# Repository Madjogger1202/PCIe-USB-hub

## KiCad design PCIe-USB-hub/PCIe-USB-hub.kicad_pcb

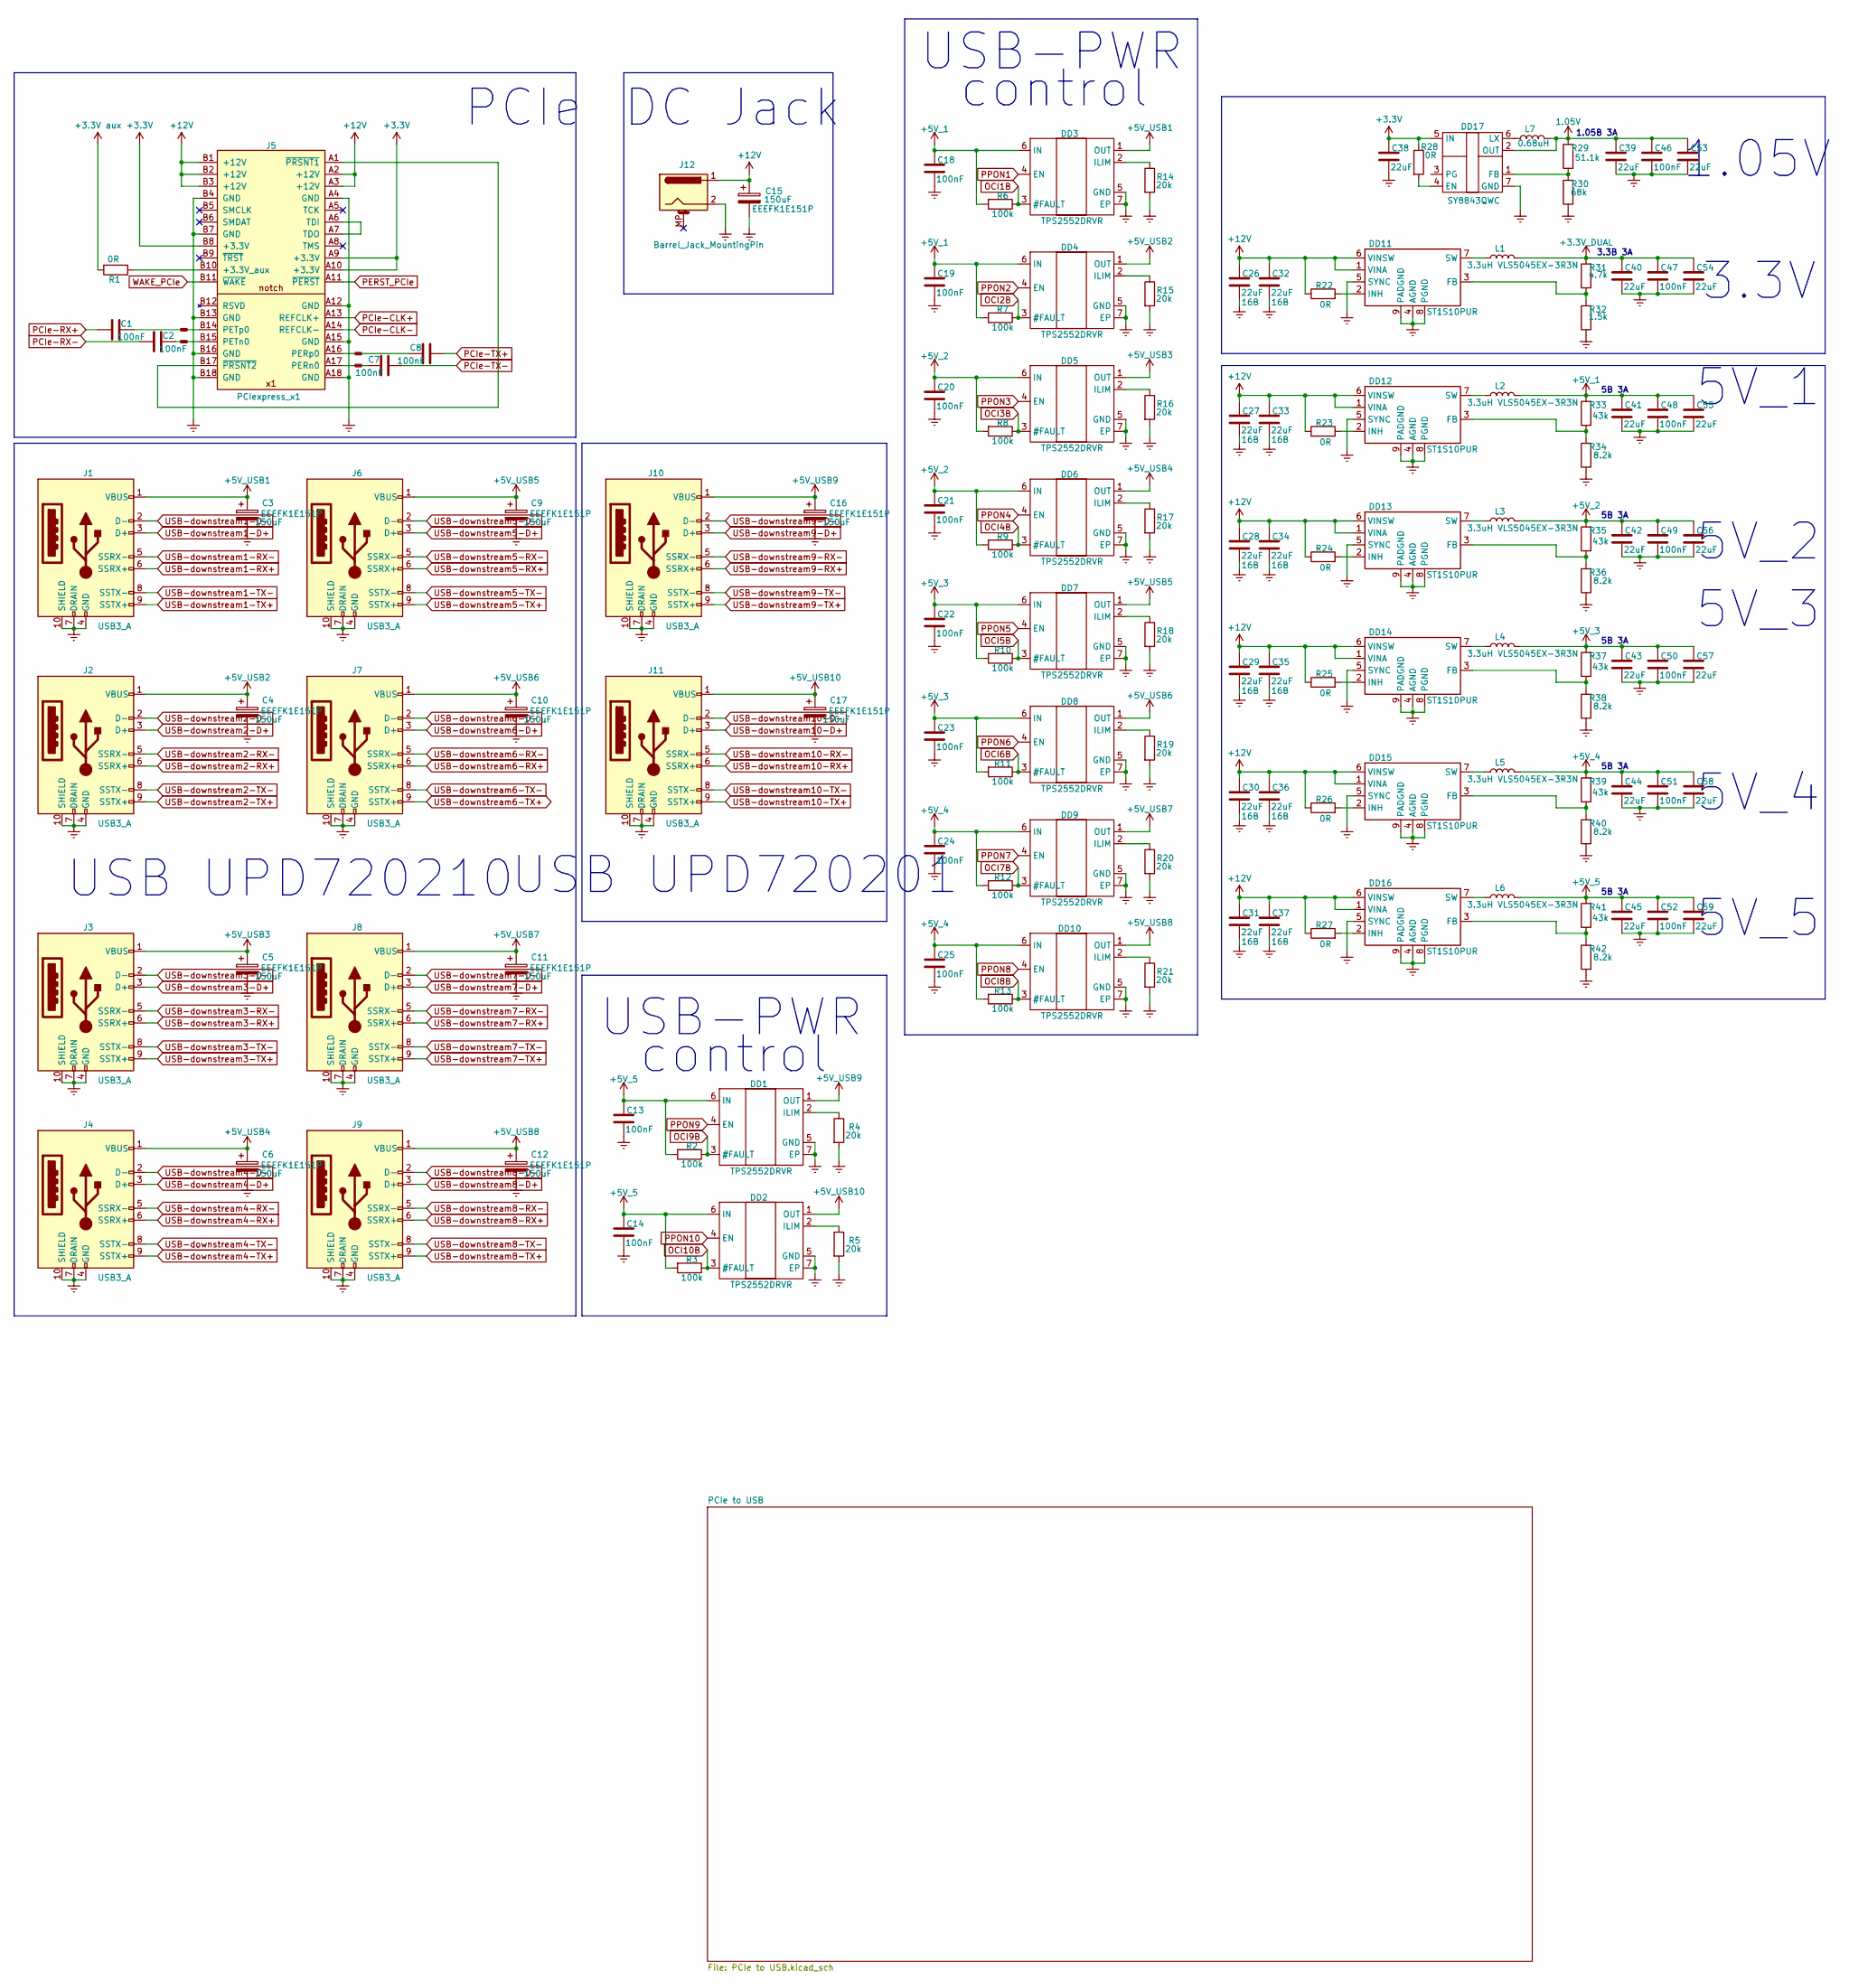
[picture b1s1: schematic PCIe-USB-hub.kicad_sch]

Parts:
C1, C2, C7, C8, C13, C14, C18, C19, C20, C21, C22, C23, C24, C25, C46, C47, C48, C49, C50, C51, C52: 100nF; C_0402_1005Metric
C3, C4, C5, C6, C9, C10, C11, C12, C15, C16, C17: EEEFK1E151P; C_Elec_8x10.2
C26, C27, C28, C29, C30, C31, C32, C33, C34, C35, C36, C37: 22uF; C_0805_2012Metric
C38, C39, C40, C41, C42, C43, C44, C45, C53, C54, C55, C56, C57, C58, C59: 22uF; C_0402_1005Metric
DD1, DD2, DD3, DD4, DD5, DD6, DD7, DD8, DD9, DD10: TPS2552DRVR; WSON-6-1EP_2x2mm_P0.65mm_EP1x1.6mm
DD11, DD12, DD13, DD14, DD15, DD16: ST1S10PUR; DFN-8-1EP_4x4mm_P0.8mm_EP2.5x3.6mm
DD17: SY8843QWC
J1, J2, J3, J4, J6, J7, J8, J9, J10, J11: USB3_A; USB3_A_Molex_48393-001
J5: PCIexpress_x1
J12: Barrel_Jack_MountingPin; BarrelJack_GCT_DCJ200-10-A_Horizontal
L1, L2, L3, L4, L5, L6: 3.3uH VLS5045EX-3R3N; COIL_5040
L7: 0.68uH; L_Cenker_CKCS4020
R1, R22, R23, R24, R25, R26, R27, R28: 0R; R_0402_1005Metric
R2, R3, R6, R7, R8, R9, R10, R11, R12, R13: 100k; R_0402_1005Metric
R4, R5, R14, R15, R16, R17, R18, R19, R20, R21: 20k; R_0402_1005Metric
R29: 51.1k; R_0402_1005Metric
R30: 68k; R_0402_1005Metric
R31: 4.7k; R_0402_1005Metric
R32: 1.5k; R_0402_1005Metric
R33, R35, R37, R39, R41: 43k; R_0402_1005Metric
R34, R36, R38, R40, R42: 8.2k; R_0402_1005Metric

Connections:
1.05V: C39.1, C46.1, C53.1, DD17.2 (OUT), L7.2, R29.2; also elsewhere on the board
+3.3V: C38.1, DD17.5 (IN), J5.A9 (+3.3V), J5.A10 (+3.3V), J5.B8 (+3.3V), R28.1
+3.3V aux: R1.2
+3.3V_DUAL: C40.1, C47.1, C54.1, L1.2, R31.2; also elsewhere on the board
+5V_1: C18.1, C19.1, C41.1, C48.1, C55.1, DD3.6 (IN), DD4.6 (IN), L2.2, R6.2, R7.2, R33.2
+5V_2: C20.1, C21.1, C42.1, C49.1, C56.1, DD5.6 (IN), DD6.6 (IN), L3.2, R8.2, R9.2, R35.2
+5V_3: C22.1, C23.1, C43.1, C50.1, C57.1, DD7.6 (IN), DD8.6 (IN), L4.2, R10.2, R11.2, R37.2
+5V_4: C24.1, C25.1, C44.1, C51.1, C58.1, DD9.6 (IN), DD10.6 (IN), L5.2, R12.2, R13.2, R39.2
+5V_5: C13.1, C14.1, C45.1, C52.1, C59.1, DD1.6 (IN), DD2.6 (IN), L6.2, R2.2, R3.2, R41.2
+5V_USB1: C3.1, DD3.1 (OUT), J1.1 (VBUS)
+5V_USB2: C4.1, DD4.1 (OUT), J2.1 (VBUS)
+5V_USB3: C5.1, DD5.1 (OUT), J3.1 (VBUS)
+5V_USB4: C6.1, DD6.1 (OUT), J4.1 (VBUS)
+5V_USB5: C9.1, DD7.1 (OUT), J6.1 (VBUS)
+5V_USB6: C10.1, DD8.1 (OUT), J7.1 (VBUS)
+5V_USB7: C11.1, DD9.1 (OUT), J8.1 (VBUS)
+5V_USB8: C12.1, DD10.1 (OUT), J9.1 (VBUS)
+5V_USB9: C16.1, DD1.1 (OUT), J10.1 (VBUS)
+5V_USB10: C17.1, DD2.1 (OUT), J11.1 (VBUS)
+12V: C15.1, C26.1, C27.1, C28.1, C29.1, C30.1, C31.1, C32.1, C33.1, C34.1, C35.1, C36.1, C37.1, DD11.1 (VINA), DD11.6 (VINSW), DD12.1 (VINA), DD12.6 (VINSW), DD13.1 (VINA), DD13.6 (VINSW), DD14.1 (VINA), DD14.6 (VINSW), DD15.1 (VINA), DD15.6 (VINSW), DD16.1 (VINA), DD16.6 (VINSW), J5.A2 (+12V), J5.A3 (+12V), J5.B1 (+12V), J5.B2 (+12V), J5.B3 (+12V), J12.1, R22.1, R23.1, R24.1, R25.1, R26.1, R27.1
Earth: C3.2, C4.2, C5.2, C6.2, C9.2, C10.2, C11.2, C12.2, C13.2, C14.2, C15.2, C16.2, C17.2, C18.2, C19.2, C20.2, C21.2, C22.2, C23.2, C24.2, C25.2, C26.2, C27.2, C28.2, C29.2, C30.2, C31.2, C32.2, C33.2, C34.2, C35.2, C36.2, C37.2, C38.2, C39.2, C40.2, C41.2, C42.2, C43.2, C44.2, C45.2, C46.2, C47.2, C48.2, C49.2, C50.2, C51.2, C52.2, C53.2, C54.2, C55.2, C56.2, C57.2, C58.2, C59.2, DD1.5 (GND), DD1.7 (EP), DD2.5 (GND), DD2.7 (EP), DD3.5 (GND), DD3.7 (EP), DD4.5 (GND), DD4.7 (EP), DD5.5 (GND), DD5.7 (EP), DD6.5 (GND), DD6.7 (EP), DD7.5 (GND), DD7.7 (EP), DD8.5 (GND), DD8.7 (EP), DD9.5 (GND), DD9.7 (EP), DD10.5 (GND), DD10.7 (EP), DD11.4 (AGND), DD11.5 (SYNC), DD11.8 (PGND), DD11.9 (PADGND), DD12.4 (AGND), DD12.5 (SYNC), DD12.8 (PGND), DD12.9 (PADGND), DD13.4 (AGND), DD13.5 (SYNC), DD13.8 (PGND), DD13.9 (PADGND), DD14.4 (AGND), DD14.5 (SYNC), DD14.8 (PGND), DD14.9 (PADGND), DD15.4 (AGND), DD15.5 (SYNC), DD15.8 (PGND), DD15.9 (PADGND), DD16.4 (AGND), DD16.5 (SYNC), DD16.8 (PGND), DD16.9 (PADGND), DD17.7 (GND), J1.4 (GND), J1.7 (DRAIN), J1.10 (SHIELD), J2.4 (GND), J2.7 (DRAIN), J2.10 (SHIELD), J3.4 (GND), J3.7 (DRAIN), J3.10 (SHIELD), J4.4 (GND), J4.7 (DRAIN), J4.10 (SHIELD), J5.A4 (GND), J5.A12 (GND), J5.A15 (GND), J5.A18 (GND), J5.B4 (GND), J5.B7 (GND), J5.B13 (GND), J5.B16 (GND), J5.B18 (GND), J6.4 (GND), J6.7 (DRAIN), J6.10 (SHIELD), J7.4 (GND), J7.7 (DRAIN), J7.10 (SHIELD), J8.4 (GND), J8.7 (DRAIN), J8.10 (SHIELD), J9.4 (GND), J9.7 (DRAIN), J9.10 (SHIELD), J10.4 (GND), J10.7 (DRAIN), J10.10 (SHIELD), J11.4 (GND), J11.7 (DRAIN), J11.10 (SHIELD), J12.2, R4.2, R5.2, R14.2, R15.2, R16.2, R17.2, R18.2, R19.2, R20.2, R21.2, R30.1, R32.1, R34.1, R36.1, R38.1, R40.1, R42.1; also elsewhere on the board
unnamed: DD1.2 (ILIM), R4.1
unnamed: DD2.2 (ILIM), R5.1
unnamed: DD3.2 (ILIM), R14.1
unnamed: DD4.2 (ILIM), R15.1
unnamed: DD5.2 (ILIM), R16.1
unnamed: DD6.2 (ILIM), R17.1
unnamed: DD7.2 (ILIM), R18.1
unnamed: DD8.2 (ILIM), R19.1
unnamed: DD9.2 (ILIM), R20.1
unnamed: DD10.2 (ILIM), R21.1
unnamed: DD11.3 (FB), R31.1, R32.2
unnamed: DD11.2 (INH), R22.2
unnamed: DD11.7 (SW), L1.1
unnamed: DD12.3 (FB), R33.1, R34.2
unnamed: DD12.2 (INH), R23.2
unnamed: DD12.7 (SW), L2.1
unnamed: DD13.3 (FB), R35.1, R36.2
unnamed: DD13.2 (INH), R24.2
unnamed: DD13.7 (SW), L3.1
unnamed: DD14.3 (FB), R37.1, R38.2
unnamed: DD14.2 (INH), R25.2
unnamed: DD14.7 (SW), L4.1
unnamed: DD15.3 (FB), R39.1, R40.2
unnamed: DD15.2 (INH), R26.2
unnamed: DD15.7 (SW), L5.1
unnamed: DD16.3 (FB), R41.1, R42.2
unnamed: DD16.2 (INH), R27.2
unnamed: DD16.7 (SW), L6.1
unnamed: DD17.4 (EN), R28.2
unnamed: DD17.1 (FB), R29.1, R30.2
unnamed: DD17.6 (LX), L7.1
unnamed: J5.B10 (+3.3V_aux), R1.1
unnamed: J5.A6 (TDI), J5.A7 (TDO)
unnamed: J5.A1 (~PRSNT1), J5.B17 (~PRSNT2)
OCI1B: DD3.3 (#FAULT), R6.1; also elsewhere on the board
OCI2B: DD4.3 (#FAULT), R7.1; also elsewhere on the board
OCI3B: DD5.3 (#FAULT), R8.1; also elsewhere on the board
OCI4B: DD6.3 (#FAULT), R9.1; also elsewhere on the board
OCI5B: DD7.3 (#FAULT), R10.1; also elsewhere on the board
OCI6B: DD8.3 (#FAULT), R11.1; also elsewhere on the board
OCI7B: DD9.3 (#FAULT), R12.1; also elsewhere on the board
OCI8B: DD10.3 (#FAULT), R13.1; also elsewhere on the board
OCI9B: DD1.3 (#FAULT), R2.1; also elsewhere on the board
OCI10B: DD2.3 (#FAULT), R3.1; also elsewhere on the board
PCIe-CLK+: J5.A13 (REFCLK+); also elsewhere on the board
PCIe-CLK-: J5.A14 (REFCLK-); also elsewhere on the board
PCIe-RX+: C1.1; also elsewhere on the board
PCIe-RX-: C2.1; also elsewhere on the board
PCIe-TX+: C8.1; also elsewhere on the board
PCIe-TX-: C7.1; also elsewhere on the board
PERST_PCIe: J5.A11 (~PERST); also elsewhere on the board
PPON1: DD3.4 (EN); also elsewhere on the board
PPON2: DD4.4 (EN); also elsewhere on the board
PPON3: DD5.4 (EN); also elsewhere on the board
PPON4: DD6.4 (EN); also elsewhere on the board
PPON5: DD7.4 (EN); also elsewhere on the board
PPON6: DD8.4 (EN); also elsewhere on the board
PPON7: DD9.4 (EN); also elsewhere on the board
PPON8: DD10.4 (EN); also elsewhere on the board
PPON9: DD1.4 (EN); also elsewhere on the board
PPON10: DD2.4 (EN); also elsewhere on the board
USB-downstream1-D+: J1.3 (D+); also elsewhere on the board
USB-downstream1-D-: J1.2 (D-); also elsewhere on the board
USB-downstream1-RX+: J1.6 (SSRX+); also elsewhere on the board
USB-downstream1-RX-: J1.5 (SSRX-); also elsewhere on the board
USB-downstream1-TX+: J1.9 (SSTX+); also elsewhere on the board
USB-downstream1-TX-: J1.8 (SSTX-); also elsewhere on the board
USB-downstream2-D+: J2.3 (D+); also elsewhere on the board
USB-downstream2-D-: J2.2 (D-); also elsewhere on the board
USB-downstream2-RX+: J2.6 (SSRX+); also elsewhere on the board
USB-downstream2-RX-: J2.5 (SSRX-); also elsewhere on the board
USB-downstream2-TX+: J2.9 (SSTX+); also elsewhere on the board
USB-downstream2-TX-: J2.8 (SSTX-); also elsewhere on the board
USB-downstream3-D+: J3.3 (D+); also elsewhere on the board
USB-downstream3-D-: J3.2 (D-); also elsewhere on the board
USB-downstream3-RX+: J3.6 (SSRX+); also elsewhere on the board
USB-downstream3-RX-: J3.5 (SSRX-); also elsewhere on the board
USB-downstream3-TX+: J3.9 (SSTX+); also elsewhere on the board
USB-downstream3-TX-: J3.8 (SSTX-); also elsewhere on the board
USB-downstream4-D+: J4.3 (D+); also elsewhere on the board
USB-downstream4-D-: J4.2 (D-); also elsewhere on the board
USB-downstream4-RX+: J4.6 (SSRX+); also elsewhere on the board
USB-downstream4-RX-: J4.5 (SSRX-); also elsewhere on the board
USB-downstream4-TX+: J4.9 (SSTX+); also elsewhere on the board
USB-downstream4-TX-: J4.8 (SSTX-); also elsewhere on the board
USB-downstream5-D+: J6.3 (D+); also elsewhere on the board
USB-downstream5-D-: J6.2 (D-); also elsewhere on the board
USB-downstream5-RX+: J6.6 (SSRX+); also elsewhere on the board
USB-downstream5-RX-: J6.5 (SSRX-); also elsewhere on the board
USB-downstream5-TX+: J6.9 (SSTX+); also elsewhere on the board
USB-downstream5-TX-: J6.8 (SSTX-); also elsewhere on the board
USB-downstream6-D+: J7.3 (D+); also elsewhere on the board
USB-downstream6-D-: J7.2 (D-); also elsewhere on the board
USB-downstream6-RX+: J7.6 (SSRX+); also elsewhere on the board
USB-downstream6-RX-: J7.5 (SSRX-); also elsewhere on the board
USB-downstream6-TX+: J7.9 (SSTX+); also elsewhere on the board
USB-downstream6-TX-: J7.8 (SSTX-); also elsewhere on the board
USB-downstream7-D+: J8.3 (D+); also elsewhere on the board
USB-downstream7-D-: J8.2 (D-); also elsewhere on the board
USB-downstream7-RX+: J8.6 (SSRX+); also elsewhere on the board
USB-downstream7-RX-: J8.5 (SSRX-); also elsewhere on the board
USB-downstream7-TX+: J8.9 (SSTX+); also elsewhere on the board
USB-downstream7-TX-: J8.8 (SSTX-); also elsewhere on the board
USB-downstream8-D+: J9.3 (D+); also elsewhere on the board
USB-downstream8-D-: J9.2 (D-); also elsewhere on the board
USB-downstream8-RX+: J9.6 (SSRX+); also elsewhere on the board
USB-downstream8-RX-: J9.5 (SSRX-); also elsewhere on the board
USB-downstream8-TX+: J9.9 (SSTX+); also elsewhere on the board
USB-downstream8-TX-: J9.8 (SSTX-); also elsewhere on the board
USB-downstream9-D+: J10.3 (D+); also elsewhere on the board
USB-downstream9-D-: J10.2 (D-); also elsewhere on the board
USB-downstream9-RX+: J10.6 (SSRX+); also elsewhere on the board
USB-downstream9-RX-: J10.5 (SSRX-); also elsewhere on the board
USB-downstream9-TX+: J10.9 (SSTX+); also elsewhere on the board
USB-downstream9-TX-: J10.8 (SSTX-); also elsewhere on the board
USB-downstream10-D+: J11.3 (D+); also elsewhere on the board
USB-downstream10-D-: J11.2 (D-); also elsewhere on the board
USB-downstream10-RX+: J11.6 (SSRX+); also elsewhere on the board
USB-downstream10-RX-: J11.5 (SSRX-); also elsewhere on the board
USB-downstream10-TX+: J11.9 (SSTX+); also elsewhere on the board
USB-downstream10-TX-: J11.8 (SSTX-); also elsewhere on the board
WAKE_PCIe: J5.B11 (~WAKE); also elsewhere on the board
_PCIe-RX+: C1.2, J5.B14 (PETp0)
_PCIe-RX-: C2.2, J5.B15 (PETn0)
_PCIe-TX+: C8.2, J5.A16 (PERp0)
_PCIe-TX-: C7.2, J5.A17 (PERn0)

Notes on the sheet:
1.05V
USB-PWR
1.05В 3А
USB UPD720210
5V_3
3.3В 3А
5В 3А
USB UPD720201
5V_5
5V_1
DC Jack
5V_2
5V_4
control
3.3V
PCIe

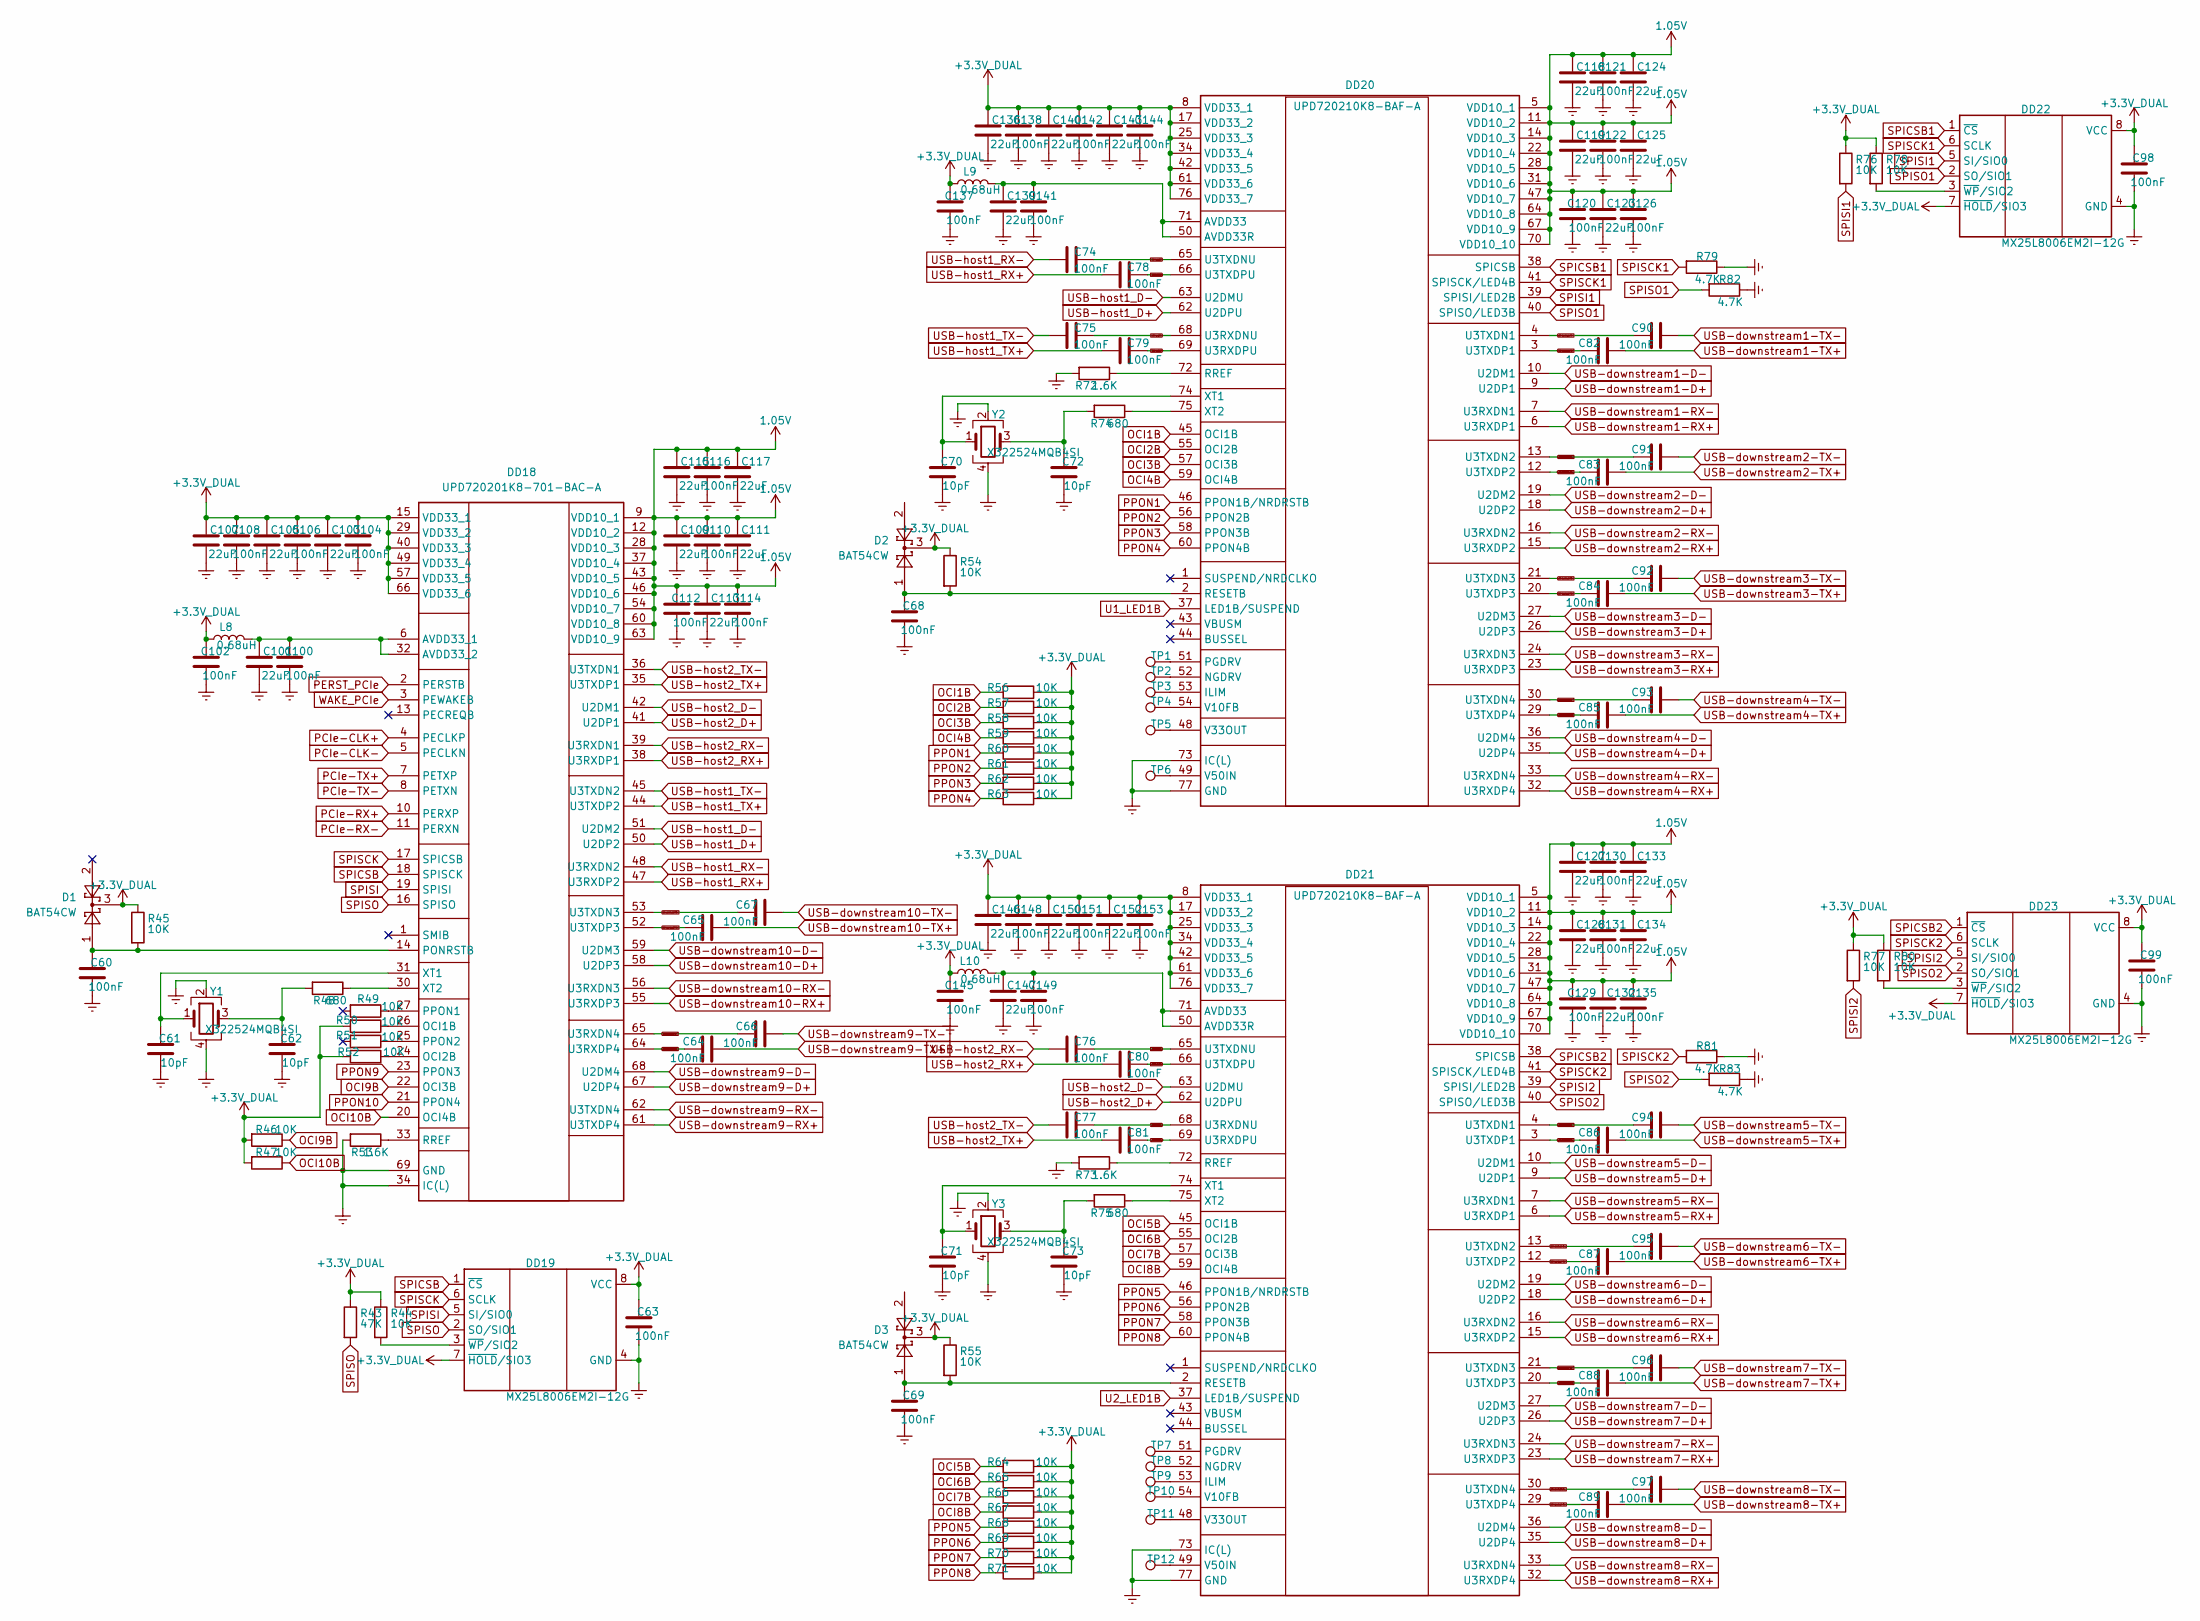
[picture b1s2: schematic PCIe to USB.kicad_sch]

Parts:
C60, C63, C64, C65, C66, C67, C68, C69, C74, C75, C76, C77, C78, C79, C80, C81, C82, C83, C84, C85, C86, C87, C88, C89, C90, C91, C92, C93, C94, C95, C96, C97, C98, C99, C100, C102, C104, C106, C108, C110, C112, C114, C116, C120, C121, C122, C126, C129, C130, C131, C135, C137, C138, C141, C142, C144, C145, C148, C149, C151, C153: 100nF; C_0402_1005Metric
C61, C62, C70, C71, C72, C73: 10pF; C_0402_1005Metric
C101, C103, C105, C107, C109, C111, C113, C115, C117, C118, C119, C123, C124, C125, C127, C128, C132, C133, C134, C136, C139, C140, C143, C146, C147, C150, C152: 22uF; C_0402_1005Metric
D1, D2, D3: BAT54CW; SOT-323_SC-70
DD18: UPD720201K8-701-BAC-A; UPD720201K8
DD19, DD22, DD23: MX25L8006EM2I-12G; SOP-8_3.9x4.9mm_P1.27mm
DD20, DD21: UPD720210K8-BAF-A; QFN-76-1EP_9x9mm_P0.4mm_EP5.81x6.31mm; Manufacturer_Part_Number UPD720210K8-BAF-A; Mouser Part Number 968-UPD720210K8BAFA
L8, L9, L10: 0.68uH; L_Cenker_CKCS4020
R43: 47K; R_0603_1608Metric
R44, R45, R46, R47, R49, R50, R51, R52, R54, R55, R56, R57, R58, R59, R60, R61, R62, R63, R64, R65, R66, R67, R68, R69, R70, R71, R76, R77, R78, R80: 10K; R_0603_1608Metric
R48, R74, R75: 680; R_0603_1608Metric
R53, R72, R73: 1.6K; R_0603_1608Metric
R79, R81, R82, R83: 4.7K; R_0603_1608Metric
TP1, TP2, TP3, TP4, TP5, TP6, TP7, TP8, TP9, TP10, TP11, TP12: TestPoint; TestPoint_Pad_D1.0mm
Y1, Y2, Y3: X322524MQB4SI; Crystal_SMD_Abracon_ABM8AIG-4Pin_3.2x2.5mm

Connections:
1.05V: C109.1, C110.1, C111.1, C112.1, C113.1, C114.1, C115.1, C116.1, C117.1, C118.1, C119.1, C120.1, C121.1, C122.1, C123.1, C124.1, C125.1, C126.1, C127.1, C128.1, C129.1, C130.1, C131.1, C132.1, C133.1, C134.1, C135.1, DD18.9 (VDD10_1), DD18.12 (VDD10_2), DD18.28 (VDD10_3), DD18.37 (VDD10_4), DD18.43 (VDD10_5), DD18.46 (VDD10_6), DD18.54 (VDD10_7), DD18.60 (VDD10_8), DD18.63 (VDD10_9), DD20.5 (VDD10_1), DD20.11 (VDD10_2), DD20.14 (VDD10_3), DD20.22 (VDD10_4), DD20.28 (VDD10_5), DD20.31 (VDD10_6), DD20.47 (VDD10_7), DD20.64 (VDD10_8), DD20.67 (VDD10_9), DD20.70 (VDD10_10), DD21.5 (VDD10_1), DD21.11 (VDD10_2), DD21.14 (VDD10_3), DD21.22 (VDD10_4), DD21.28 (VDD10_5), DD21.31 (VDD10_6), DD21.47 (VDD10_7), DD21.64 (VDD10_8), DD21.67 (VDD10_9), DD21.70 (VDD10_10); also elsewhere on the board
+3.3V_DUAL: C63.1, C98.1, C99.1, C102.1, C103.1, C104.1, C105.1, C106.1, C107.1, C108.1, C136.1, C137.1, C138.1, C140.1, C142.1, C143.1, C144.1, C145.1, C146.1, C148.1, C150.1, C151.1, C152.1, C153.1, D1.3, D2.3, D3.3, DD18.15 (VDD33_1), DD18.29 (VDD33_2), DD18.40 (VDD33_3), DD18.49 (VDD33_4), DD18.57 (VDD33_5), DD18.66 (VDD33_6), DD19.7 (~HOLD/SIO3), DD19.8 (VCC), DD20.8 (VDD33_1), DD20.17 (VDD33_2), DD20.25 (VDD33_3), DD20.34 (VDD33_4), DD20.42 (VDD33_5), DD20.61 (VDD33_6), DD20.76 (VDD33_7), DD21.8 (VDD33_1), DD21.17 (VDD33_2), DD21.25 (VDD33_3), DD21.34 (VDD33_4), DD21.42 (VDD33_5), DD21.61 (VDD33_6), DD21.76 (VDD33_7), DD22.7 (~HOLD/SIO3), DD22.8 (VCC), DD23.7 (~HOLD/SIO3), DD23.8 (VCC), L8.1, L9.1, L10.1, R43.1, R44.1, R45.1, R46.2, R47.2, R50.2, R52.2, R54.1, R55.1, R56.1, R57.1, R58.1, R59.1, R60.1, R61.1, R62.1, R63.1, R64.1, R65.1, R66.1, R67.1, R68.1, R69.1, R70.1, R71.1, R76.1, R77.1, R78.1, R80.1; also elsewhere on the board
Earth: C60.2, C61.2, C62.2, C63.2, C68.2, C69.2, C70.2, C71.2, C72.2, C73.2, C98.2, C99.2, C100.2, C101.2, C102.2, C103.2, C104.2, C105.2, C106.2, C107.2, C108.2, C109.2, C110.2, C111.2, C112.2, C113.2, C114.2, C115.2, C116.2, C117.2, C118.2, C119.2, C120.2, C121.2, C122.2, C123.2, C124.2, C125.2, C126.2, C127.2, C128.2, C129.2, C130.2, C131.2, C132.2, C133.2, C134.2, C135.2, C136.2, C137.2, C138.2, C139.2, C140.2, C141.2, C142.2, C143.2, C144.2, C145.2, C146.2, C147.2, C148.2, C149.2, C150.2, C151.2, C152.2, C153.2, DD18.34 (IC(L)), DD18.69 (GND), DD19.4 (GND), DD20.73 (IC(L)), DD20.77 (GND), DD21.73 (IC(L)), DD21.77 (GND), DD22.4 (GND), DD23.4 (GND), R53.2, R72.2, R73.2, R79.1, R81.1, R82.1, R83.1, Y1.2, Y1.4, Y2.2, Y2.4, Y3.2, Y3.4; also elsewhere on the board
unnamed: C62.1, R48.2, Y1.3
unnamed: C72.1, R74.2, Y2.3
unnamed: C73.1, R75.2, Y3.3
unnamed: C100.1, C101.1, DD18.6 (AVDD33_1), DD18.32 (AVDD33_2), L8.2
unnamed: DD18.26 (OCI1B), R50.1
unnamed: DD18.24 (OCI2B), R52.1
unnamed: C60.1, D1.1, DD18.14 (PONRSTB), R45.2
unnamed: DD18.27 (PPON1), R49.1
unnamed: DD18.25 (PPON2), R51.1
unnamed: DD18.33 (RREF), R53.1
unnamed: C61.1, DD18.31 (XT1), Y1.1
unnamed: DD18.30 (XT2), R48.1
unnamed: DD19.3 (~WP/SIO2), R44.2
unnamed: C139.1, C141.1, DD20.50 (AVDD33R), DD20.71 (AVDD33), L9.2
unnamed: DD20.53 (ILIM), TP3.1
unnamed: DD20.52 (NGDRV), TP2.1
unnamed: DD20.51 (PGDRV), TP1.1
unnamed: C68.1, D2.1, DD20.2 (RESETB), R54.2
unnamed: DD20.72 (RREF), R72.1
unnamed: DD20.54 (V10FB), TP4.1
unnamed: DD20.48 (V33OUT), TP5.1
unnamed: DD20.49 (V50IN), TP6.1
unnamed: C70.1, DD20.74 (XT1), Y2.1
unnamed: DD20.75 (XT2), R74.1
unnamed: C147.1, C149.1, DD21.50 (AVDD33R), DD21.71 (AVDD33), L10.2
unnamed: DD21.53 (ILIM), TP9.1
unnamed: DD21.52 (NGDRV), TP8.1
unnamed: DD21.51 (PGDRV), TP7.1
unnamed: C69.1, D3.1, DD21.2 (RESETB), R55.2
unnamed: DD21.72 (RREF), R73.1
unnamed: DD21.54 (V10FB), TP10.1
unnamed: DD21.48 (V33OUT), TP11.1
unnamed: DD21.49 (V50IN), TP12.1
unnamed: C71.1, DD21.74 (XT1), Y3.1
unnamed: DD21.75 (XT2), R75.1
unnamed: DD22.3 (~WP/SIO2), R78.2
unnamed: DD23.3 (~WP/SIO2), R80.2
OCI1B: DD20.45 (OCI1B), R56.2; also elsewhere on the board
OCI2B: DD20.55 (OCI2B), R57.2; also elsewhere on the board
OCI3B: DD20.57 (OCI3B), R58.2; also elsewhere on the board
OCI4B: DD20.59 (OCI4B), R59.2; also elsewhere on the board
OCI5B: DD21.45 (OCI1B), R64.2; also elsewhere on the board
OCI6B: DD21.55 (OCI2B), R65.2; also elsewhere on the board
OCI7B: DD21.57 (OCI3B), R66.2; also elsewhere on the board
OCI8B: DD21.59 (OCI4B), R67.2; also elsewhere on the board
OCI9B: DD18.22 (OCI3B), R46.1; also elsewhere on the board
OCI10B: DD18.20 (OCI4B), R47.1; also elsewhere on the board
PCIe-CLK+: DD18.4 (PECLKP); also elsewhere on the board
PCIe-CLK-: DD18.5 (PECLKN); also elsewhere on the board
PCIe-RX+: DD18.10 (PERXP); also elsewhere on the board
PCIe-RX-: DD18.11 (PERXN); also elsewhere on the board
PCIe-TX+: DD18.7 (PETXP); also elsewhere on the board
PCIe-TX-: DD18.8 (PETXN); also elsewhere on the board
PERST_PCIe: DD18.2 (PERSTB); also elsewhere on the board
PPON1: DD20.46 (PPON1B/NRDRSTB), R60.2; also elsewhere on the board
PPON2: DD20.56 (PPON2B), R61.2; also elsewhere on the board
PPON3: DD20.58 (PPON3B), R62.2; also elsewhere on the board
PPON4: DD20.60 (PPON4B), R63.2; also elsewhere on the board
PPON5: DD21.46 (PPON1B/NRDRSTB), R68.2; also elsewhere on the board
PPON6: DD21.56 (PPON2B), R69.2; also elsewhere on the board
PPON7: DD21.58 (PPON3B), R70.2; also elsewhere on the board
PPON8: DD21.60 (PPON4B), R71.2; also elsewhere on the board
PPON9: DD18.23 (PPON3); also elsewhere on the board
PPON10: DD18.21 (PPON4); also elsewhere on the board
SPICSB: DD18.18 (SPISCK), DD19.1 (~CS)
SPICSB1: DD20.38 (SPICSB), DD22.1 (~CS)
SPICSB2: DD21.38 (SPICSB), DD23.1 (~CS)
SPISCK: DD18.17 (SPICSB), DD19.6 (SCLK)
SPISCK1: DD20.41 (SPISCK/LED4B), DD22.6 (SCLK), R79.2
SPISCK2: DD21.41 (SPISCK/LED4B), DD23.6 (SCLK), R81.2
SPISI: DD18.19 (SPISI), DD19.5 (SI/SIO0)
SPISI1: DD20.39 (SPISI/LED2B), DD22.5 (SI/SIO0), R76.2
SPISI2: DD21.39 (SPISI/LED2B), DD23.5 (SI/SIO0), R77.2
SPISO: DD18.16 (SPISO), DD19.2 (SO/SIO1), R43.2
SPISO1: DD20.40 (SPISO/LED3B), DD22.2 (SO/SIO1), R82.2
SPISO2: DD21.40 (SPISO/LED3B), DD23.2 (SO/SIO1), R83.2
U1_LED1B: DD20.37 (LED1B/SUSPEND)
U2_LED1B: DD21.37 (LED1B/SUSPEND)
USB-downstream1-D+: DD20.9 (U2DP1); also elsewhere on the board
USB-downstream1-D-: DD20.10 (U2DM1); also elsewhere on the board
USB-downstream1-RX+: DD20.6 (U3RXDP1); also elsewhere on the board
USB-downstream1-RX-: DD20.7 (U3RXDN1); also elsewhere on the board
USB-downstream1-TX+: C82.1; also elsewhere on the board
USB-downstream1-TX-: C90.1; also elsewhere on the board
USB-downstream2-D+: DD20.18 (U2DP2); also elsewhere on the board
USB-downstream2-D-: DD20.19 (U2DM2); also elsewhere on the board
USB-downstream2-RX+: DD20.15 (U3RXDP2); also elsewhere on the board
USB-downstream2-RX-: DD20.16 (U3RXDN2); also elsewhere on the board
USB-downstream2-TX+: C83.1; also elsewhere on the board
USB-downstream2-TX-: C91.1; also elsewhere on the board
USB-downstream3-D+: DD20.26 (U2DP3); also elsewhere on the board
USB-downstream3-D-: DD20.27 (U2DM3); also elsewhere on the board
USB-downstream3-RX+: DD20.23 (U3RXDP3); also elsewhere on the board
USB-downstream3-RX-: DD20.24 (U3RXDN3); also elsewhere on the board
USB-downstream3-TX+: C84.1; also elsewhere on the board
USB-downstream3-TX-: C92.1; also elsewhere on the board
USB-downstream4-D+: DD20.35 (U2DP4); also elsewhere on the board
USB-downstream4-D-: DD20.36 (U2DM4); also elsewhere on the board
USB-downstream4-RX+: DD20.32 (U3RXDP4); also elsewhere on the board
USB-downstream4-RX-: DD20.33 (U3RXDN4); also elsewhere on the board
USB-downstream4-TX+: C85.1; also elsewhere on the board
USB-downstream4-TX-: C93.1; also elsewhere on the board
USB-downstream5-D+: DD21.9 (U2DP1); also elsewhere on the board
USB-downstream5-D-: DD21.10 (U2DM1); also elsewhere on the board
USB-downstream5-RX+: DD21.6 (U3RXDP1); also elsewhere on the board
USB-downstream5-RX-: DD21.7 (U3RXDN1); also elsewhere on the board
USB-downstream5-TX+: C86.1; also elsewhere on the board
USB-downstream5-TX-: C94.1; also elsewhere on the board
USB-downstream6-D+: DD21.18 (U2DP2); also elsewhere on the board
USB-downstream6-D-: DD21.19 (U2DM2); also elsewhere on the board
USB-downstream6-RX+: DD21.15 (U3RXDP2); also elsewhere on the board
USB-downstream6-RX-: DD21.16 (U3RXDN2); also elsewhere on the board
USB-downstream6-TX+: C87.1; also elsewhere on the board
USB-downstream6-TX-: C95.1; also elsewhere on the board
USB-downstream7-D+: DD21.26 (U2DP3); also elsewhere on the board
USB-downstream7-D-: DD21.27 (U2DM3); also elsewhere on the board
USB-downstream7-RX+: DD21.23 (U3RXDP3); also elsewhere on the board
USB-downstream7-RX-: DD21.24 (U3RXDN3); also elsewhere on the board
USB-downstream7-TX+: C88.1; also elsewhere on the board
USB-downstream7-TX-: C96.1; also elsewhere on the board
USB-downstream8-D+: DD21.35 (U2DP4); also elsewhere on the board
USB-downstream8-D-: DD21.36 (U2DM4); also elsewhere on the board
USB-downstream8-RX+: DD21.32 (U3RXDP4); also elsewhere on the board
USB-downstream8-RX-: DD21.33 (U3RXDN4); also elsewhere on the board
USB-downstream8-TX+: C89.1; also elsewhere on the board
USB-downstream8-TX-: C97.1; also elsewhere on the board
USB-downstream9-D+: DD18.67 (U2DP4); also elsewhere on the board
USB-downstream9-D-: DD18.68 (U2DM4); also elsewhere on the board
USB-downstream9-RX+: DD18.61 (U3TXDP4); also elsewhere on the board
USB-downstream9-RX-: DD18.62 (U3TXDN4); also elsewhere on the board
USB-downstream9-TX+: C64.1; also elsewhere on the board
USB-downstream9-TX-: C66.1; also elsewhere on the board
USB-downstream10-D+: DD18.58 (U2DP3); also elsewhere on the board
USB-downstream10-D-: DD18.59 (U2DM3); also elsewhere on the board
USB-downstream10-RX+: DD18.55 (U3RXDP3); also elsewhere on the board
USB-downstream10-RX-: DD18.56 (U3RXDN3); also elsewhere on the board
USB-downstream10-TX+: C65.1; also elsewhere on the board
USB-downstream10-TX-: C67.1; also elsewhere on the board
USB-host1_D+: DD18.50 (U2DP2), DD20.62 (U2DPU)
USB-host1_D-: DD18.51 (U2DM2), DD20.63 (U2DMU)
USB-host1_RX+: C78.1, DD18.47 (U3RXDP2)
USB-host1_RX-: C74.1, DD18.48 (U3RXDN2)
USB-host1_TX+: C79.1, DD18.44 (U3TXDP2)
USB-host1_TX-: C75.1, DD18.45 (U3TXDN2)
USB-host2_D+: DD18.41 (U2DP1), DD21.62 (U2DPU)
USB-host2_D-: DD18.42 (U2DM1), DD21.63 (U2DMU)
USB-host2_RX+: C80.1, DD18.38 (U3RXDP1)
USB-host2_RX-: C76.1, DD18.39 (U3RXDN1)
USB-host2_TX+: C81.1, DD18.35 (U3TXDP1)
USB-host2_TX-: C77.1, DD18.36 (U3TXDN1)
WAKE_PCIe: DD18.3 (PEWAKEB); also elsewhere on the board
_USB-downstream1-TX+: C82.2, DD20.3 (U3TXDP1)
_USB-downstream1-TX-: C90.2, DD20.4 (U3TXDN1)
_USB-downstream2-TX+: C83.2, DD20.12 (U3TXDP2)
_USB-downstream2-TX-: C91.2, DD20.13 (U3TXDN2)
_USB-downstream3-TX+: C84.2, DD20.20 (U3TXDP3)
_USB-downstream3-TX-: C92.2, DD20.21 (U3TXDN3)
_USB-downstream4-TX+: C85.2, DD20.29 (U3TXDP4)
_USB-downstream4-TX-: C93.2, DD20.30 (U3TXDN4)
_USB-downstream5-TX+: C86.2, DD21.3 (U3TXDP1)
_USB-downstream5-TX-: C94.2, DD21.4 (U3TXDN1)
_USB-downstream6-TX+: C87.2, DD21.12 (U3TXDP2)
_USB-downstream6-TX-: C95.2, DD21.13 (U3TXDN2)
_USB-downstream7-TX+: C88.2, DD21.20 (U3TXDP3)
_USB-downstream7-TX-: C96.2, DD21.21 (U3TXDN3)
_USB-downstream8-TX+: C89.2, DD21.29 (U3TXDP4)
_USB-downstream8-TX-: C97.2, DD21.30 (U3TXDN4)
_USB-downstream9-TX+: C64.2, DD18.64 (U3RXDP4)
_USB-downstream9-TX-: C66.2, DD18.65 (U3RXDN4)
_USB-downstream10-TX+: C65.2, DD18.52 (U3TXDP3)
_USB-downstream10-TX-: C67.2, DD18.53 (U3TXDN3)
_USB-host1_RX+: C78.2, DD20.66 (U3TXDPU)
_USB-host1_RX-: C74.2, DD20.65 (U3TXDNU)
_USB-host1_TX+: C79.2, DD20.69 (U3RXDPU)
_USB-host1_TX-: C75.2, DD20.68 (U3RXDNU)
_USB-host2_RX+: C80.2, DD21.66 (U3TXDPU)
_USB-host2_RX-: C76.2, DD21.65 (U3TXDNU)
_USB-host2_TX+: C81.2, DD21.69 (U3RXDPU)
_USB-host2_TX-: C77.2, DD21.68 (U3RXDNU)
